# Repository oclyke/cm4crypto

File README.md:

# cm4crypto

cm4crypto is an adapter board that allows you to use an M-Key M.2 compatible module with the Raspberry Pi Compute Module 4 (cm4).

adding fast terabyte SSD options within a sleek RPi 4 format makes the cm4crypto perfect for uses like:
* participating in blockchain networks
* acting as a home media server
* hosting a local database

## status

this project is no longer actively developed.
the source material will continue to be available for reference.

additional resources:

* [onshape model](https://cad.onshape.com/documents/3095ac02ee5d7dd8a1b9e12a/w/86bdcc88d4120b9515956abd/e/6d8a025f4a8b2a44825a6443?renderMode=0&uiState=6629d60ecf655f459d6d604c)
* [time lapse of routing the board](https://youtu.be/ZWktmO8pLDk)

## features

* Adds M.2 M-Key PCIe x1 interface for use with NVMe SSDs or other compatible modules
* Designed for use in the [Flirc RPi 4 case](https://flirc.tv/more/raspberry-pi-4-case)
* Power Over Ethernet (PoE) support
* Camera Interface

# M.2 compatibility

M.2 specifies a connector layout, standard interfaces, and a few form factors. with such a wide variety of options available no single product can hope to support them all. here are the things you should check to see if your desired module is compatible:

property | value | notes
--- | ------- | ------
key | **M** | the M.2 connector on the cm4crypto uses an **M key**
interface | **PCIe x1** | though the M key standard supports PCIe x4 the cm4 only has x1 PCIe lane available. thanks to PCIe compatibility this should only reduce performance, not prevent functionality
dimensions | up to **22 x 80** mm | to fit in the case 

## RPi 4 compatibility

the cm4rypto inherently gains some compatibility with RPi 4 accessories since it was designed to work with the sleek Flirc case however design tradeoffs had to be made as well. 

### compatible

* 1x Gigabit ethernet
* 2x micro HDMI ports
* 1x USB-C port for power or USB OTG
* 1x USB-A port (USB 2.0)

### discrepancies

* there is **no 3.5mm audio jack**
* **GPIO is very limited** - only GPIO 2, 3, and 14 are available along with the first set of power pins (for PoE compatibility)
* the **camera interface is relocated** so that it comes out near the sd card
* the **sd card receptacle is slightly offset** to allow for the M.2 connector

## compatible / recommended products

### cases
* [Flirc Raspberry Pi 4 Case](https://flirc.tv/more/raspberry-pi-4-case)

### PoE hats
* [CMC Tech 3.5A](https://cctvfactory.com/copy-of-cmc-tech-5-2v-3-5a-17-5watt-power-over-ethernet-poe-hat-for-raspberry-pi-4-model-b-and-pi-3-model-b-ieee-802-3af-or-802-3at-poe-network-standard-compliant-made-in-rpc/) (available on Amazon)
* 

# show and tell

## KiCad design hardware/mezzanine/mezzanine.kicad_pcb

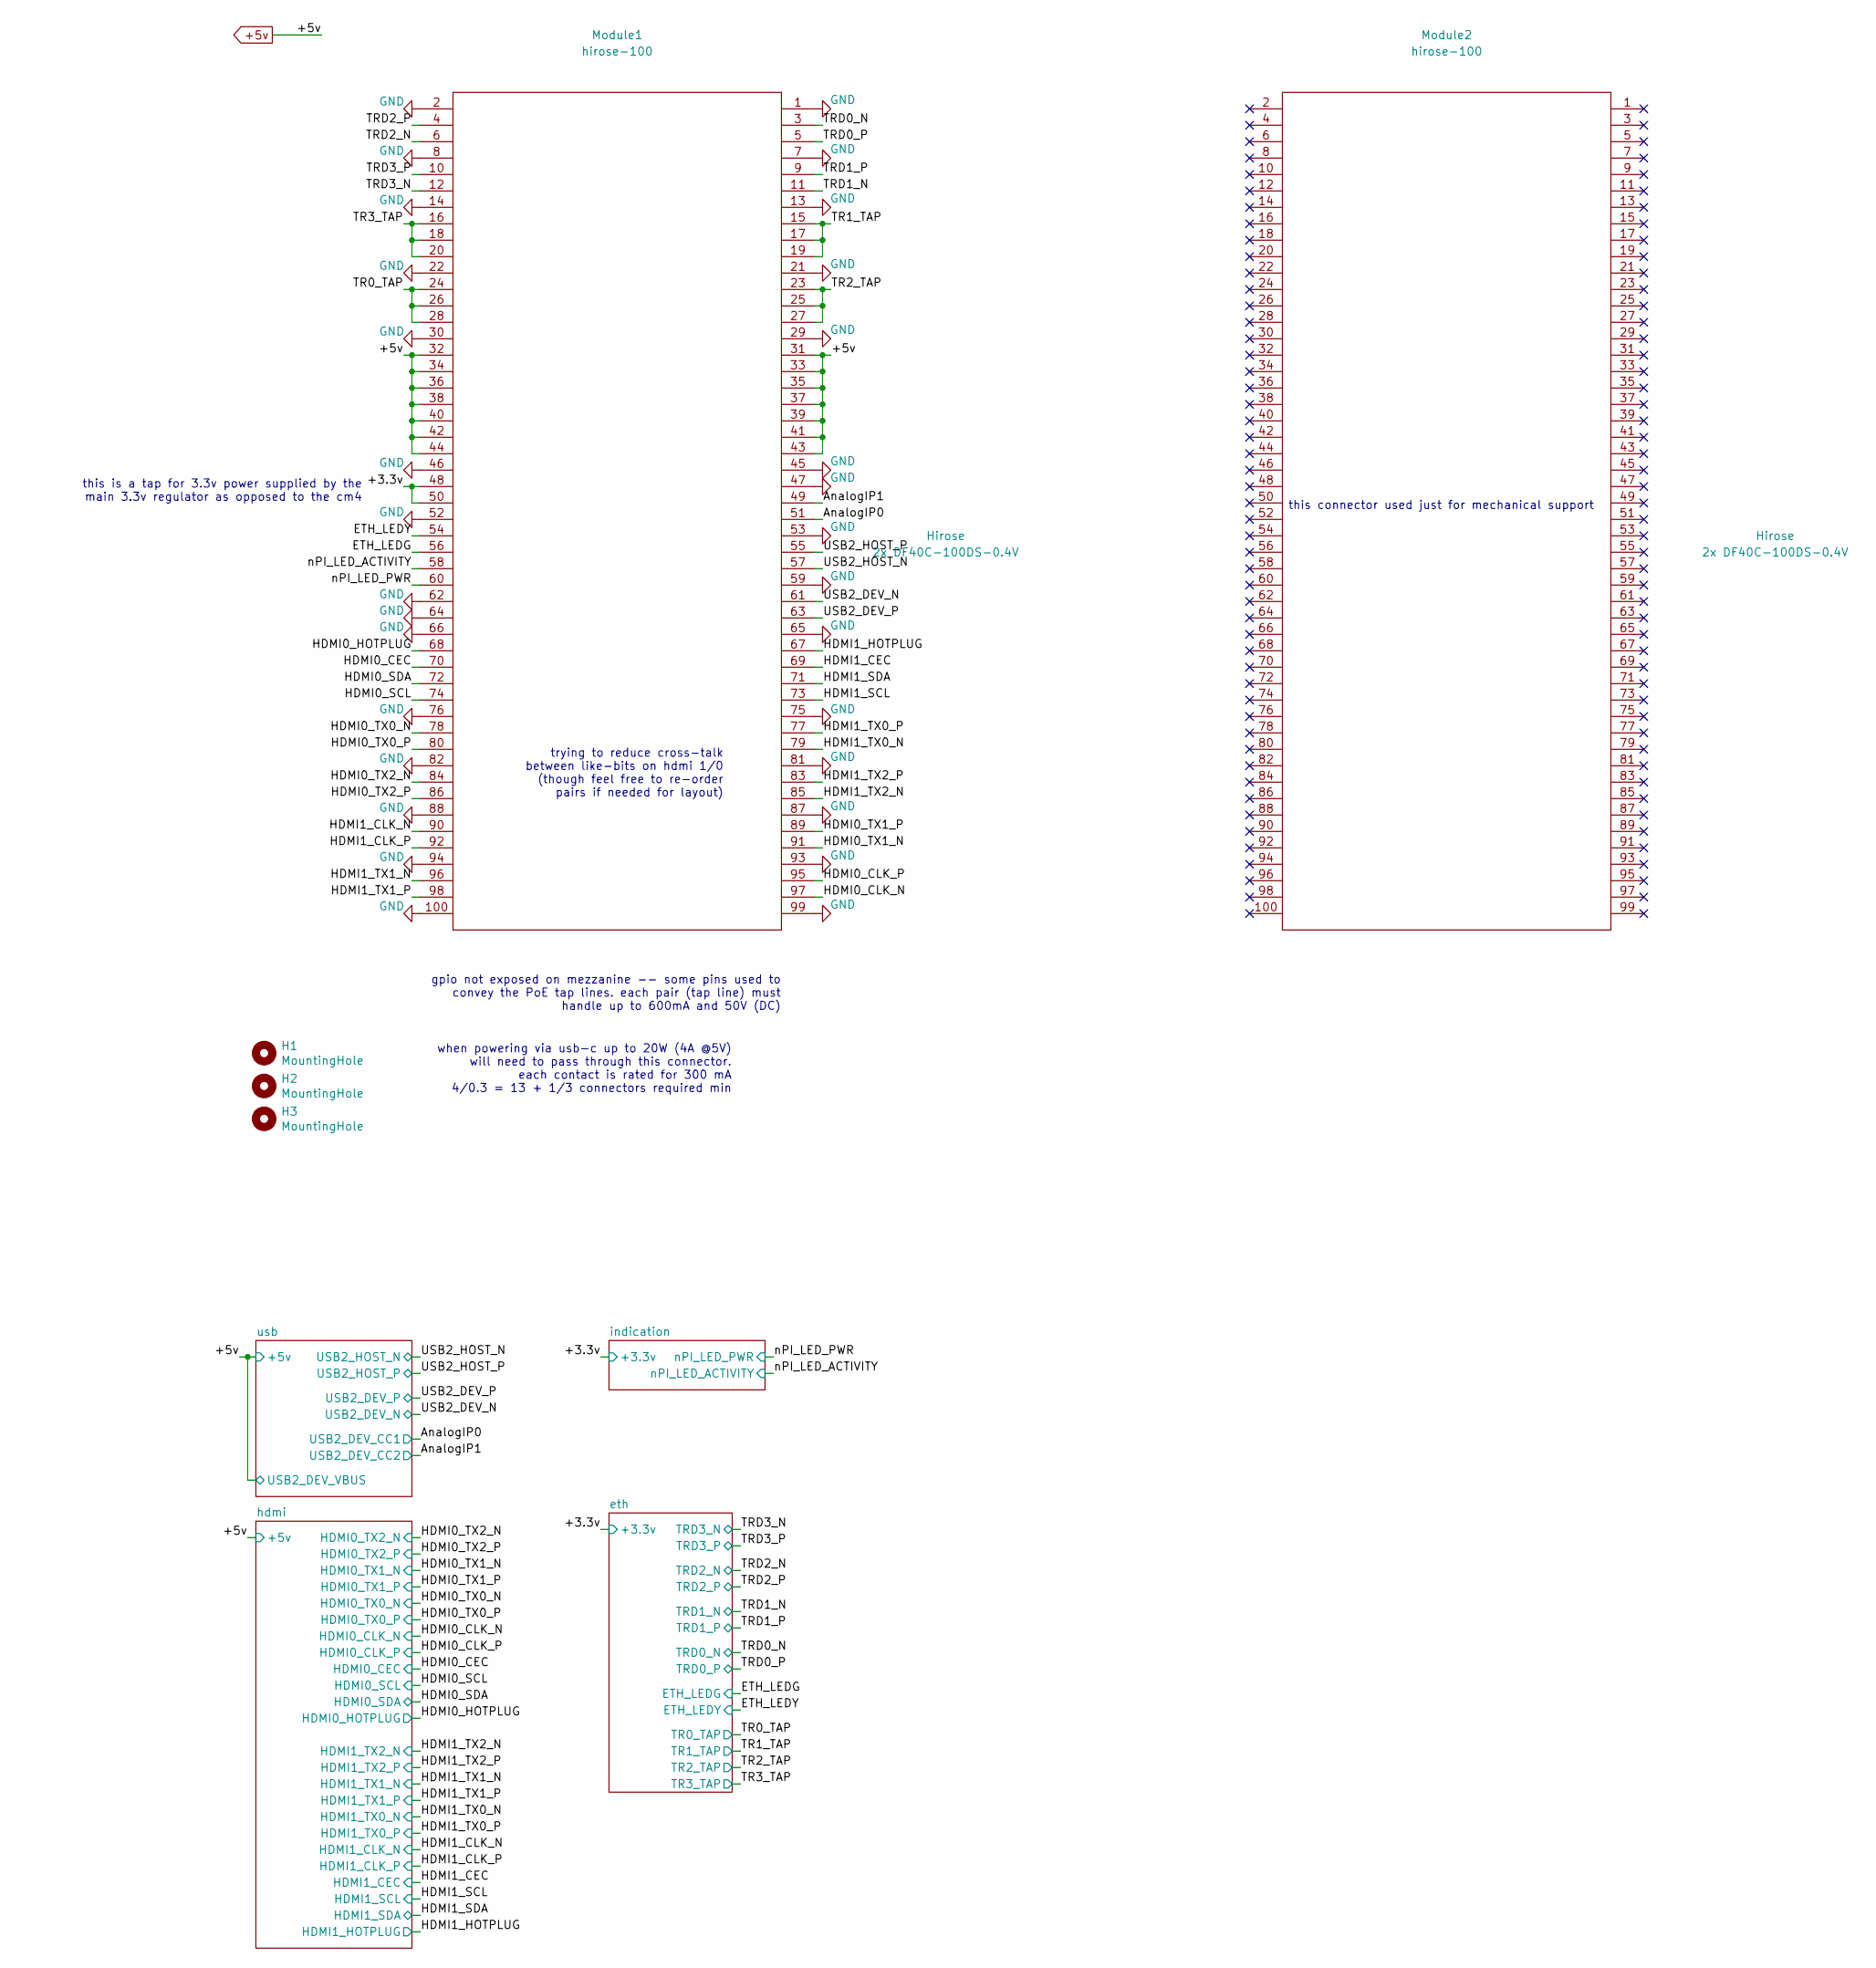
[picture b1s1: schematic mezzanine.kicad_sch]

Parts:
H1, H2, H3: MountingHole; MountingHole_2.7mm_M2.5
Module1, Module2: hirose-100; DF40C-100DP-0.4V(51)

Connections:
+5v: Module1.31, Module1.32, Module1.33, Module1.34, Module1.35, Module1.36, Module1.37, Module1.38, Module1.39, Module1.40, Module1.41, Module1.42, Module1.43, Module1.44; also elsewhere on the board
/+3.3v: Module1.48, Module1.50; also elsewhere on the board
/AnalogIP0: Module1.51
/AnalogIP1: Module1.49
/ETH_LEDG: Module1.56; also elsewhere on the board
/ETH_LEDY: Module1.54; also elsewhere on the board
/HDMI0_CEC: Module1.70; also elsewhere on the board
/HDMI0_CLK_N: Module1.97; also elsewhere on the board
/HDMI0_CLK_P: Module1.95; also elsewhere on the board
/HDMI0_HOTPLUG: Module1.68; also elsewhere on the board
/HDMI0_SCL: Module1.74; also elsewhere on the board
/HDMI0_SDA: Module1.72; also elsewhere on the board
/HDMI0_TX0_N: Module1.78; also elsewhere on the board
/HDMI0_TX0_P: Module1.80; also elsewhere on the board
/HDMI0_TX1_N: Module1.91; also elsewhere on the board
/HDMI0_TX1_P: Module1.89; also elsewhere on the board
/HDMI0_TX2_N: Module1.84; also elsewhere on the board
/HDMI0_TX2_P: Module1.86; also elsewhere on the board
/HDMI1_CEC: Module1.69; also elsewhere on the board
/HDMI1_CLK_N: Module1.90; also elsewhere on the board
/HDMI1_CLK_P: Module1.92; also elsewhere on the board
/HDMI1_HOTPLUG: Module1.67; also elsewhere on the board
/HDMI1_SCL: Module1.73; also elsewhere on the board
/HDMI1_SDA: Module1.71; also elsewhere on the board
/HDMI1_TX0_N: Module1.79; also elsewhere on the board
/HDMI1_TX0_P: Module1.77; also elsewhere on the board
/HDMI1_TX1_N: Module1.96; also elsewhere on the board
/HDMI1_TX1_P: Module1.98; also elsewhere on the board
/HDMI1_TX2_N: Module1.85; also elsewhere on the board
/HDMI1_TX2_P: Module1.83; also elsewhere on the board
/TR0_TAP: Module1.24, Module1.26, Module1.28; also elsewhere on the board
/TR1_TAP: Module1.15, Module1.17, Module1.19; also elsewhere on the board
/TR2_TAP: Module1.23, Module1.25, Module1.27; also elsewhere on the board
/TR3_TAP: Module1.16, Module1.18, Module1.20; also elsewhere on the board
/TRD0_N: Module1.3; also elsewhere on the board
/TRD0_P: Module1.5; also elsewhere on the board
/TRD1_N: Module1.11; also elsewhere on the board
/TRD1_P: Module1.9; also elsewhere on the board
/TRD2_N: Module1.6; also elsewhere on the board
/TRD2_P: Module1.4; also elsewhere on the board
/TRD3_N: Module1.12; also elsewhere on the board
/TRD3_P: Module1.10; also elsewhere on the board
/USB2_DEV_N: Module1.61; also elsewhere on the board
/USB2_DEV_P: Module1.63; also elsewhere on the board
/USB2_HOST_N: Module1.57; also elsewhere on the board
/USB2_HOST_P: Module1.55; also elsewhere on the board
/nPI_LED_ACTIVITY: Module1.58; also elsewhere on the board
/nPI_LED_PWR: Module1.60; also elsewhere on the board
GND: Module1.1, Module1.2, Module1.7, Module1.8, Module1.13, Module1.14, Module1.21, Module1.22, Module1.29, Module1.30, Module1.45, Module1.46, Module1.47, Module1.52, Module1.53, Module1.59, Module1.62, Module1.64, Module1.65, Module1.66, Module1.75, Module1.76, Module1.81, Module1.82, Module1.87, Module1.88, Module1.93, Module1.94, Module1.99, Module1.100; also elsewhere on the board

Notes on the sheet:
this is a tap for 3.3v power supplied by the main 3.3v regulator as opposed to the cm4
trying to reduce cross-talk between like-bits on hdmi 1/0 (though feel free to re-order pairs if needed for layout)
when powering via usb-c up to 20W (4A @5V) will need to pass through this connector. each contact is rated for 300 mA 4/0.3 = 13 + 1/3 connectors required min
gpio not exposed on mezzanine -- some pins used to convey the PoE tap lines. each pair (tap line) must handle up to 600mA and 50V (DC)
this connector used just for mechanical support

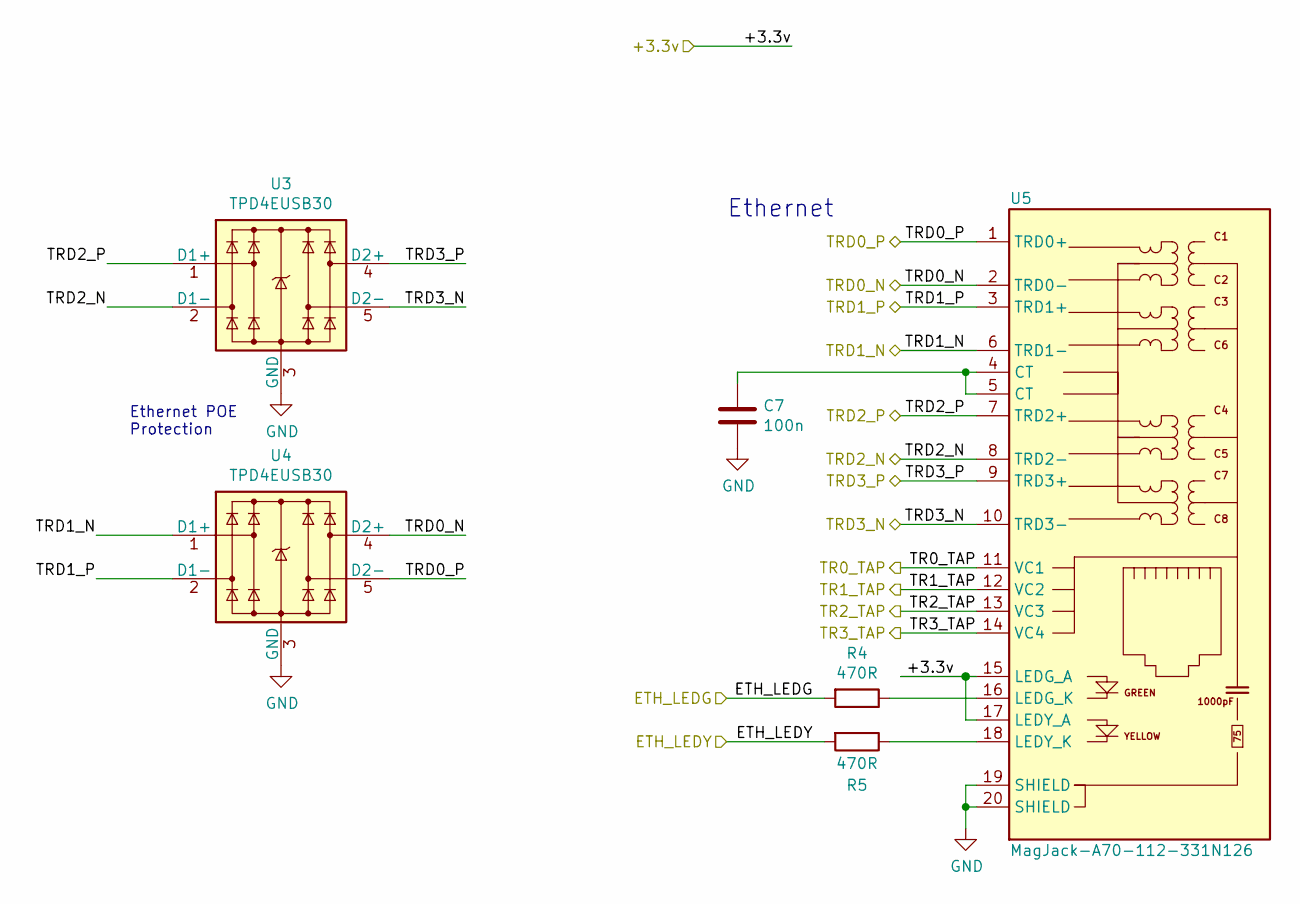
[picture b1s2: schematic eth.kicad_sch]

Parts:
C7: 100n; C_0603_1608Metric
R4, R5: 470R; R_0603_1608Metric
U3, U4: TPD4EUSB30; USON-10_2.5x1.0mm_P0.5mm; Part Description Quad TVS diode for high speed signals (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
U5: MagJack-A70-112-331N126; TRJG0926HENL; Part Description Gigabit Ethernet Magjack

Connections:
/+3.3v: U5.15 (LEDG_A), U5.17 (LEDY_A); also elsewhere on the board
/ETH_LEDG: R4.2; also elsewhere on the board
/ETH_LEDY: R5.2; also elsewhere on the board
/TR0_TAP: U5.11 (VC1); also elsewhere on the board
/TR1_TAP: U5.12 (VC2); also elsewhere on the board
/TR2_TAP: U5.13 (VC3); also elsewhere on the board
/TR3_TAP: U5.14 (VC4); also elsewhere on the board
/TRD0_N: U4.4 (D2+), U4.7, U5.2 (TRD0-); also elsewhere on the board
/TRD0_P: U4.5 (D2-), U4.6, U5.1 (TRD0+); also elsewhere on the board
/TRD1_N: U4.1 (D1+), U4.10, U5.6 (TRD1-); also elsewhere on the board
/TRD1_P: U4.2 (D1-), U4.9, U5.3 (TRD1+); also elsewhere on the board
/TRD2_N: U3.2 (D1-), U3.9, U5.8 (TRD2-); also elsewhere on the board
/TRD2_P: U3.1 (D1+), U3.10, U5.7 (TRD2+); also elsewhere on the board
/TRD3_N: U3.5 (D2-), U3.6, U5.10 (TRD3-); also elsewhere on the board
/TRD3_P: U3.4 (D2+), U3.7, U5.9 (TRD3+); also elsewhere on the board
GND: C7.2, U3.3 (GND), U3.8 (GND), U4.3 (GND), U4.8 (GND), U5.19 (SHIELD), U5.20 (SHIELD); also elsewhere on the board
unnamed: C7.1, U5.4 (CT), U5.5 (CT)
unnamed: R4.1, U5.16 (LEDG_K)
unnamed: R5.1, U5.18 (LEDY_K)

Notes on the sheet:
Ethernet POE Protection
Ethernet

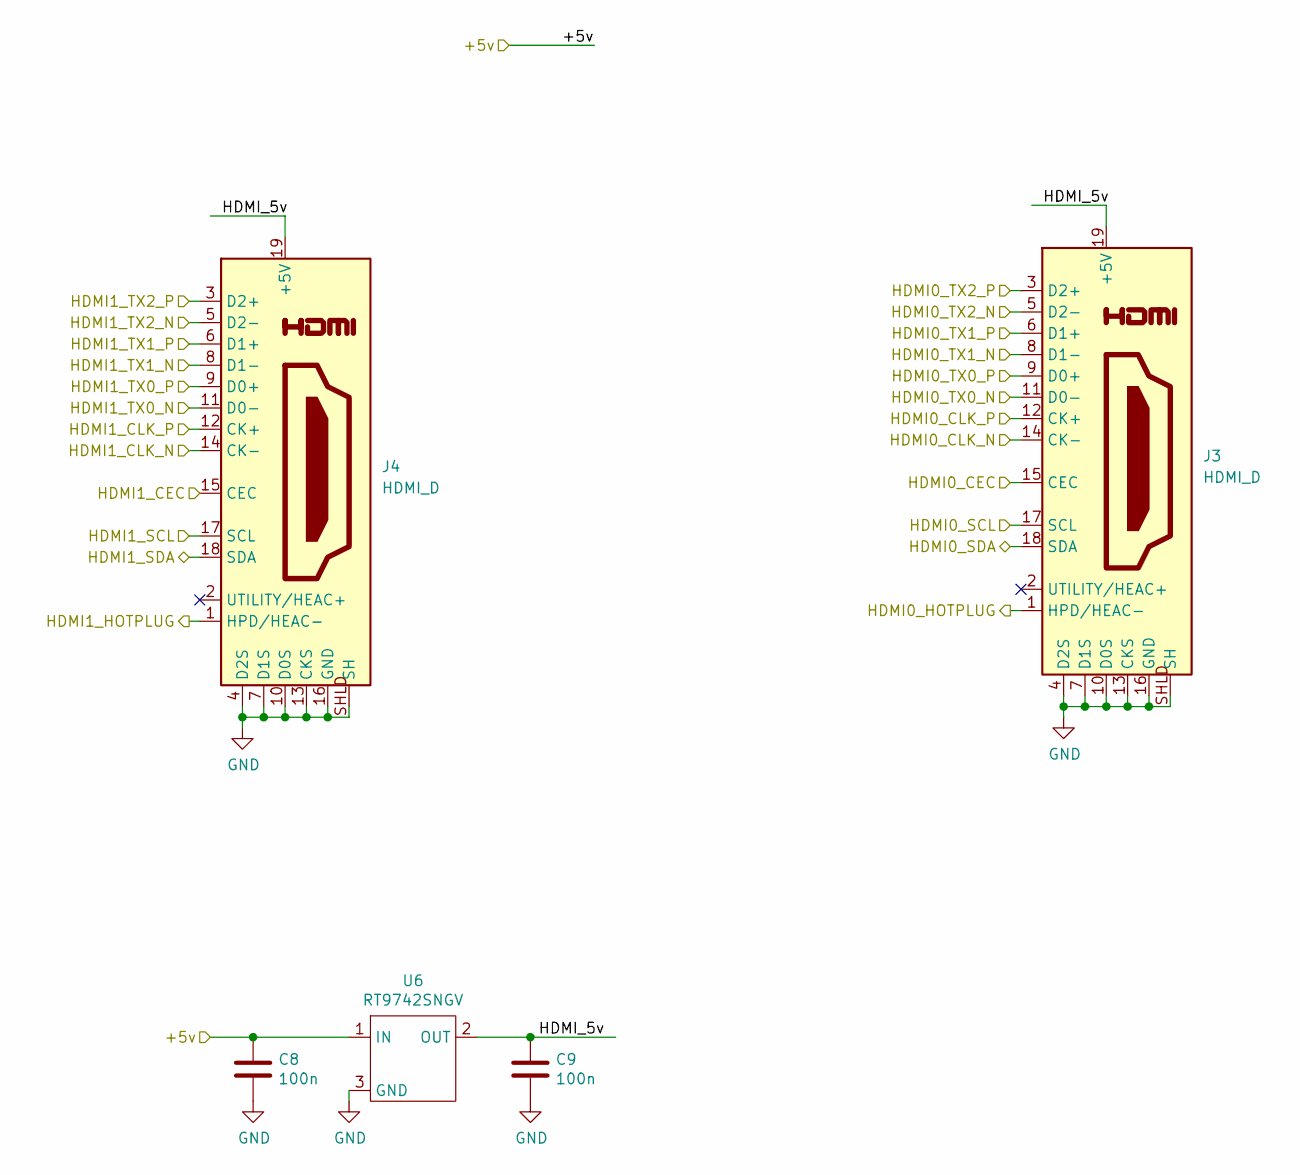
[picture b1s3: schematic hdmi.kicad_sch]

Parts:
C8, C9: 100n; C_0603_1608Metric
J3, J4: HDMI_D; HD-RA-DSF12-TR
U6: RT9742SNGV; SOT-23; Part Description Power Switch/Driver 1:1 N-Channel 500mA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

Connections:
+5v: C8.1, U6.1 (IN); also elsewhere on the board
/HDMI0_CEC: J3.15 (CEC); also elsewhere on the board
/HDMI0_CLK_N: J3.14 (CK-); also elsewhere on the board
/HDMI0_CLK_P: J3.12 (CK+); also elsewhere on the board
/HDMI0_HOTPLUG: J3.1 (HPD/HEAC-); also elsewhere on the board
/HDMI0_SCL: J3.17 (SCL); also elsewhere on the board
/HDMI0_SDA: J3.18 (SDA); also elsewhere on the board
/HDMI0_TX0_N: J3.11 (D0-); also elsewhere on the board
/HDMI0_TX0_P: J3.9 (D0+); also elsewhere on the board
/HDMI0_TX1_N: J3.8 (D1-); also elsewhere on the board
/HDMI0_TX1_P: J3.6 (D1+); also elsewhere on the board
/HDMI0_TX2_N: J3.5 (D2-); also elsewhere on the board
/HDMI0_TX2_P: J3.3 (D2+); also elsewhere on the board
/HDMI1_CEC: J4.15 (CEC); also elsewhere on the board
/HDMI1_CLK_N: J4.14 (CK-); also elsewhere on the board
/HDMI1_CLK_P: J4.12 (CK+); also elsewhere on the board
/HDMI1_HOTPLUG: J4.1 (HPD/HEAC-); also elsewhere on the board
/HDMI1_SCL: J4.17 (SCL); also elsewhere on the board
/HDMI1_SDA: J4.18 (SDA); also elsewhere on the board
/HDMI1_TX0_N: J4.11 (D0-); also elsewhere on the board
/HDMI1_TX0_P: J4.9 (D0+); also elsewhere on the board
/HDMI1_TX1_N: J4.8 (D1-); also elsewhere on the board
/HDMI1_TX1_P: J4.6 (D1+); also elsewhere on the board
/HDMI1_TX2_N: J4.5 (D2-); also elsewhere on the board
/HDMI1_TX2_P: J4.3 (D2+); also elsewhere on the board
/hdmi/HDMI_5v: C9.1, J3.19 (+5V), J4.19 (+5V), U6.2 (OUT)
GND: C8.2, C9.2, J3.4 (D2S), J3.7 (D1S), J3.10 (D0S), J3.13 (CKS), J3.16 (GND), J3.SHLD (SH), J4.4 (D2S), J4.7 (D1S), J4.10 (D0S), J4.13 (CKS), J4.16 (GND), J4.SHLD (SH), U6.3 (GND); also elsewhere on the board

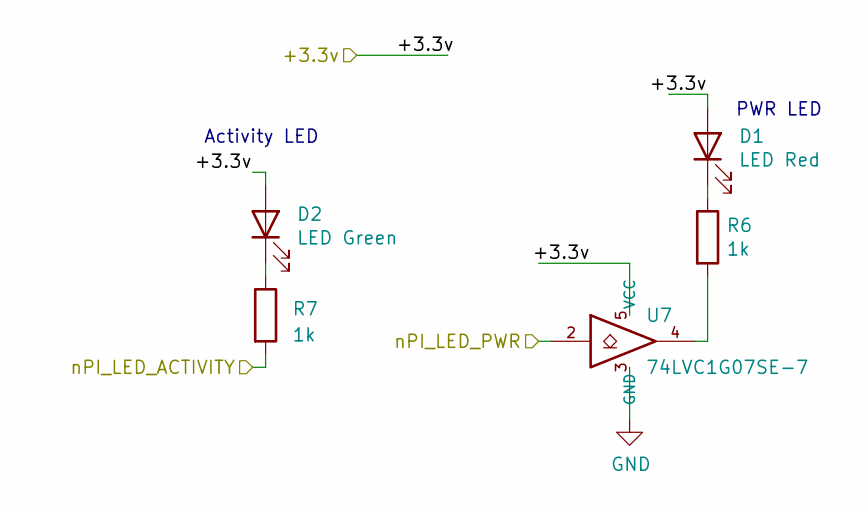
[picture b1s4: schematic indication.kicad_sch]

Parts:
D1: LED Red; LED_0603_1608Metric
D2: LED Green; LED_0603_1608Metric
R6, R7: 1k; R_0603_1608Metric
U7: 74LVC1G07SE-7; SOT-353_SC-70-5; Part Description Buffer, Non-Inverting 1 Element 1 Bit p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

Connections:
/+3.3v: D1.2 (A), D2.2 (A), U7.5 (VCC); also elsewhere on the board
/nPI_LED_ACTIVITY: R7.2; also elsewhere on the board
/nPI_LED_PWR: U7.2; also elsewhere on the board
GND: U7.3 (GND); also elsewhere on the board
unnamed: D1.1 (K), R6.1
unnamed: D2.1 (K), R7.1
unnamed: R6.2, U7.4

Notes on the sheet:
Activity LED
PWR LED

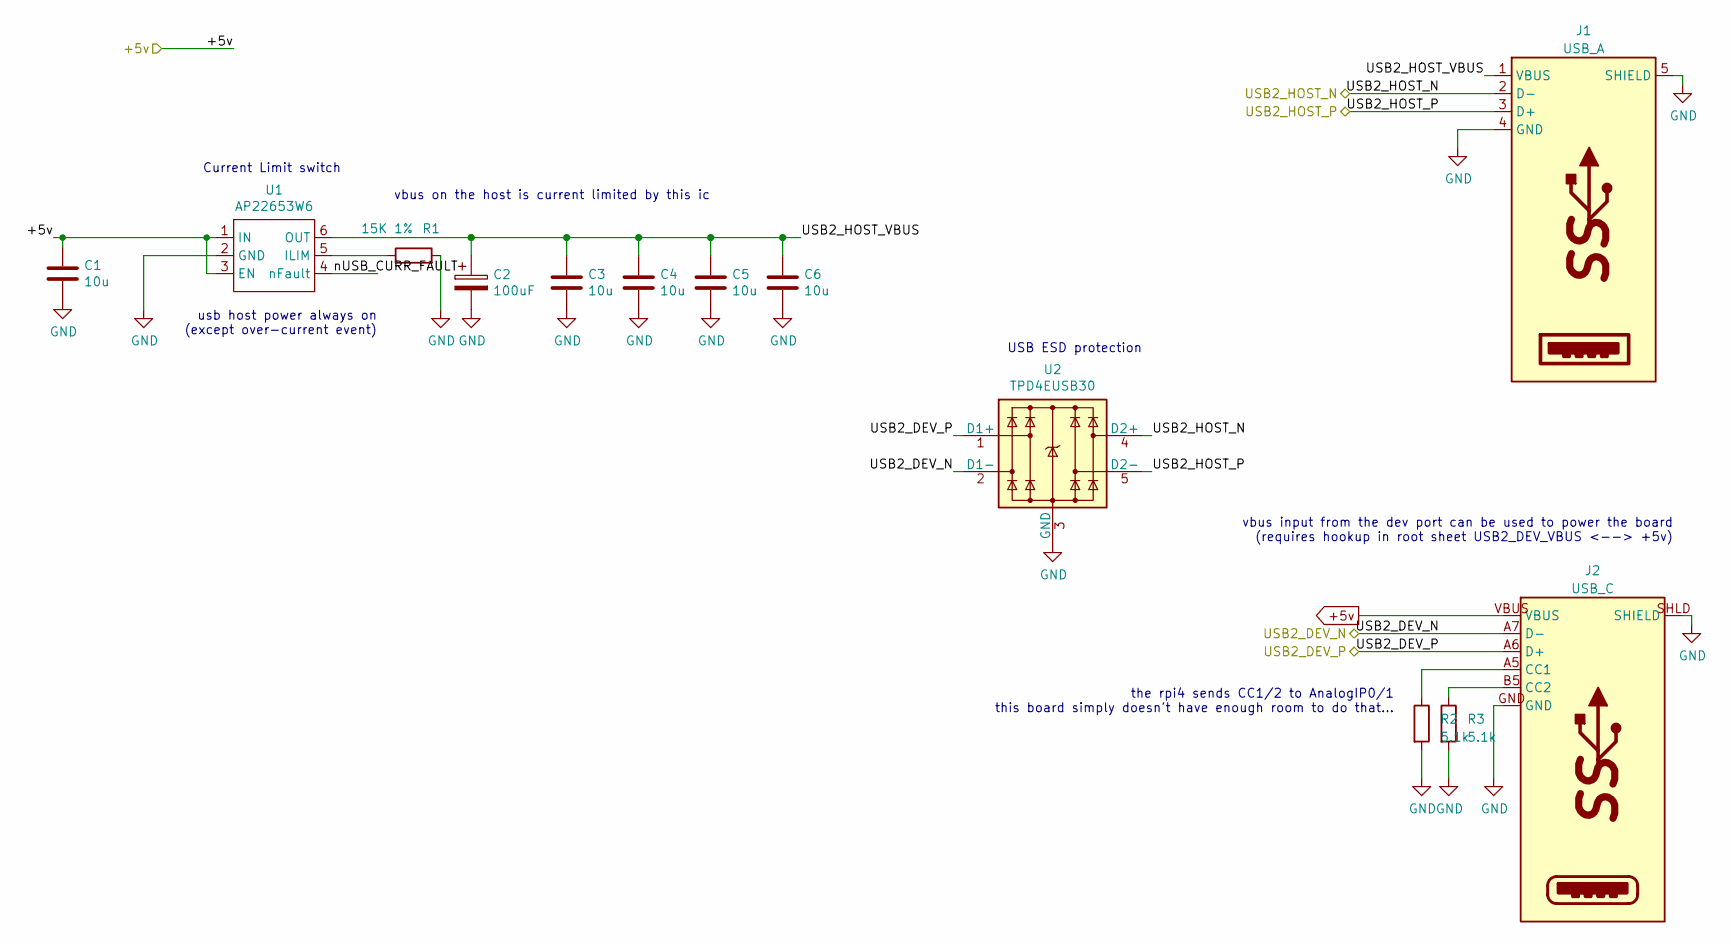
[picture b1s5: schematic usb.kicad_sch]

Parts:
C1, C3, C4, C5, C6: 10u; C_0603_1608Metric
C2: 100uF; C_0805_2012Metric_Pad1.18x1.45mm_HandSolder; Part Description Capacitor, SP-Cap, 100u, 6.3V, 15mR ESR
J1: USB_A; AU-Y1006
J2: USB_C; USB4105-GF-A
R1: 15K 1%; R_0603_1608Metric
R2, R3: 5.1k; R_0603_1608Metric
U1: AP22653W6; SOT-23-6; Part Description Power Switch/Driver 1:1 P-Channel 2.1A 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
U2: TPD4EUSB30; USON-10_2.5x1.0mm_P0.5mm; Part Description Quad TVS diode for high speed signals (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

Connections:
+5v: C1.1, J2.VBUS, U1.1 (IN), U1.3 (EN); also elsewhere on the board
/USB2_DEV_N: J2.A7 (D-), J2.B7 (D-), U2.2 (D1-), U2.9; also elsewhere on the board
/USB2_DEV_P: J2.A6 (D+), J2.B6 (D+), U2.1 (D1+), U2.10; also elsewhere on the board
/USB2_HOST_N: J1.2 (D-), U2.4 (D2+), U2.7; also elsewhere on the board
/USB2_HOST_P: J1.3 (D+), U2.5 (D2-), U2.6; also elsewhere on the board
/usb/USB2_HOST_VBUS: C2.1, C3.1, C4.1, C5.1, C6.1, J1.1 (VBUS), U1.6 (OUT)
/usb/nUSB_CURR_FAULT: U1.4 (nFault)
GND: C1.2, C2.2, C3.2, C4.2, C5.2, C6.2, J1.4 (GND), J1.5 (SHIELD), J2.GND, J2.SHLD (SHIELD), R1.2, R2.2, R3.2, U1.2 (GND), U2.3 (GND), U2.8 (GND); also elsewhere on the board
unnamed: J2.A5 (CC1), R2.1
unnamed: J2.B5 (CC2), R3.1
unnamed: R1.1, U1.5 (ILIM)

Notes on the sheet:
Current Limit switch
usb host power always on (except over-current event)
vbus on the host is current limited by this ic
USB ESD protection
the rpi4 sends CC1/2 to AnalogIP0/1 this board simply doesn't have enough room to do that...
vbus input from the dev port can be used to power the board (requires hookup in root sheet USB2_DEV_VBUS <--> +5v)

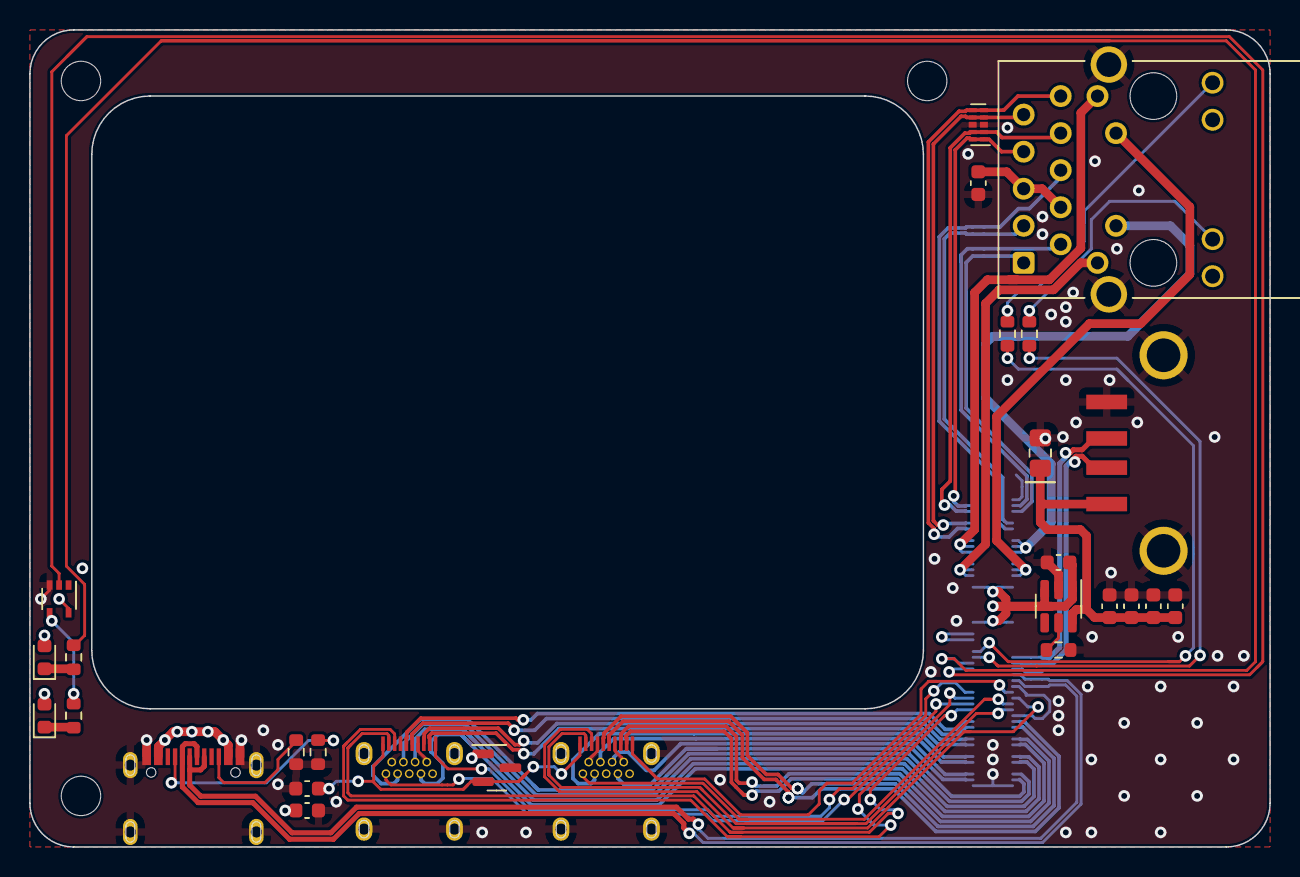
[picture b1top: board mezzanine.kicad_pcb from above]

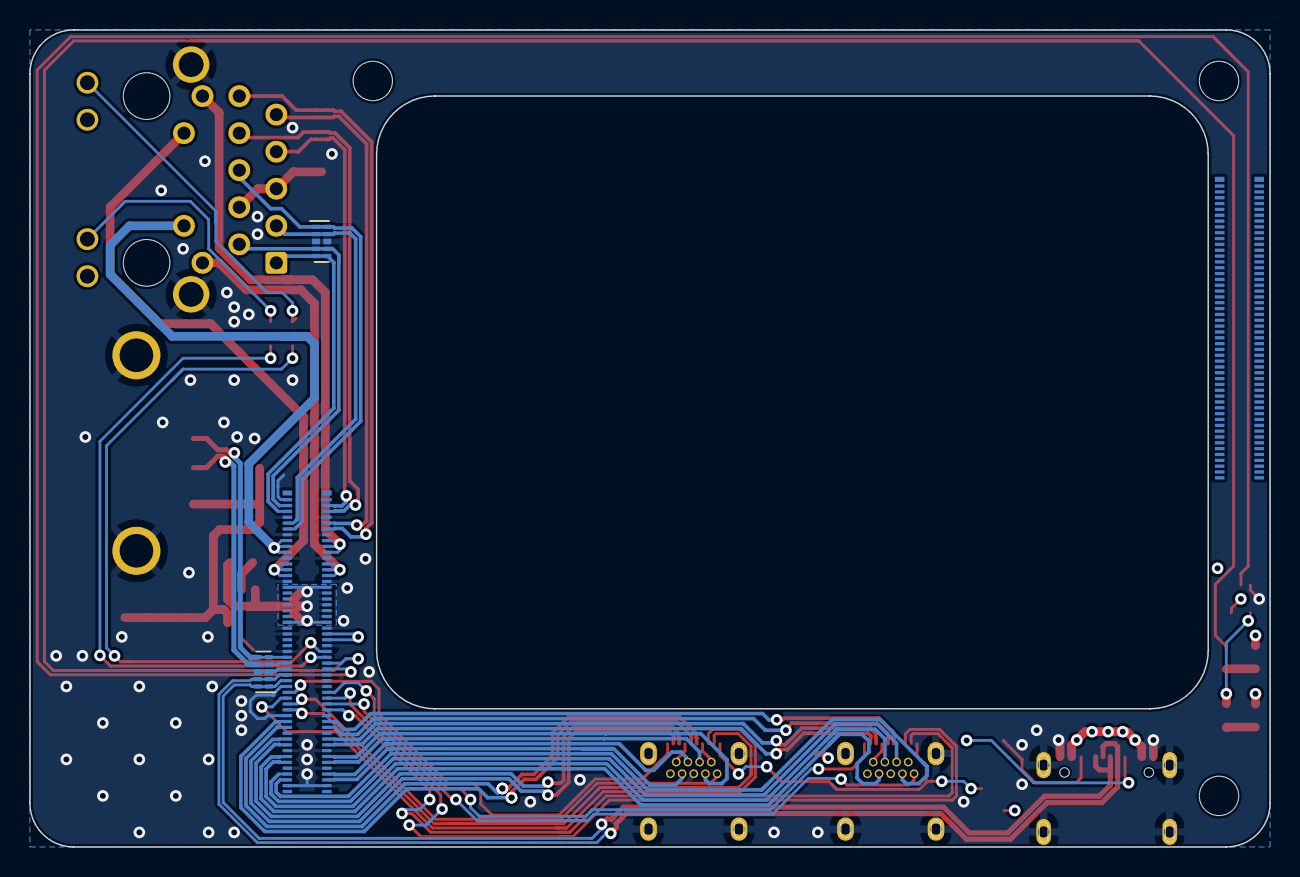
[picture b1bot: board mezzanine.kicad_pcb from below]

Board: 4 copper layers, 85.0 x 56.0 mm, 34 parts (4 on the bottom side), 58 nets.
